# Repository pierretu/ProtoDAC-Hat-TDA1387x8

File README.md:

# ProtoDAC Hat+ TDA1387x8 Rotary Encoder

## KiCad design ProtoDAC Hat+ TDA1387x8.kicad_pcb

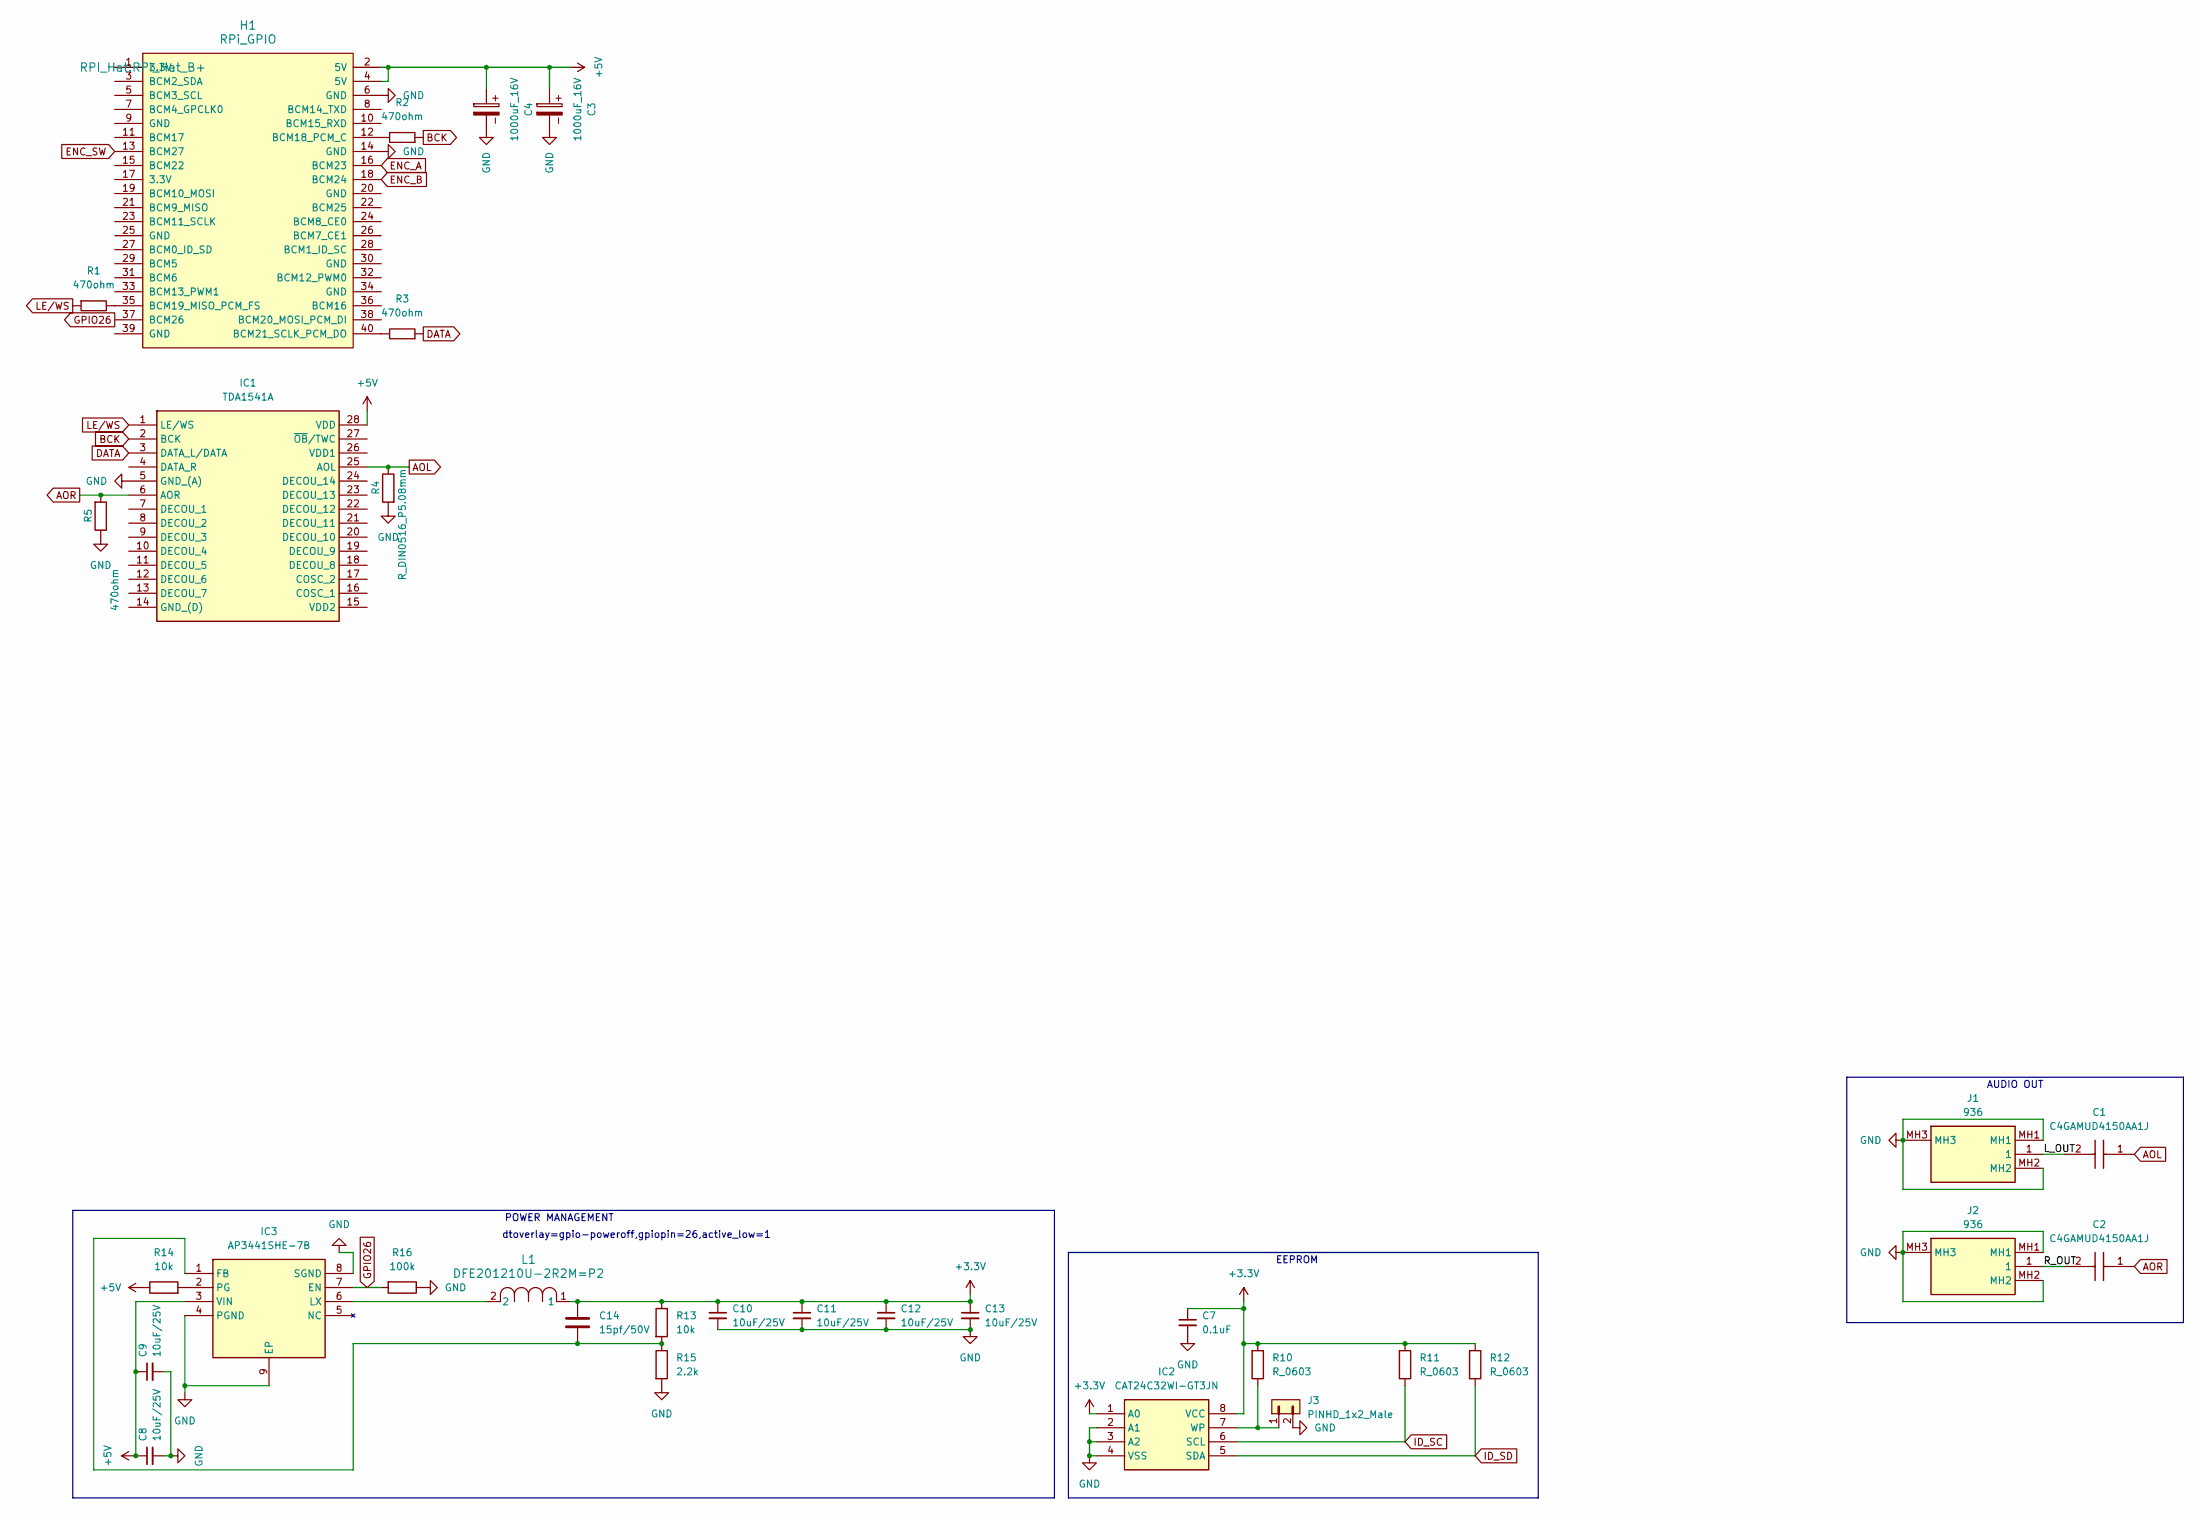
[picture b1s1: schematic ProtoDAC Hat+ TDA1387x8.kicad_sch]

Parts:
C1, C2: C4GAMUD4150AA1J; CAPPA14200W120L4400D2450; Manufacturer_Part_Number C4GAMUD4150AA1J
C3, C4: 1000uF_16V; CP_Radial_D10.0mm_P5.00mm
C7: 0.1uF_0603_16V; C_0603_1608Metric; Part Number 0603YC104KAT2A; JLCPCB ID C14663
C8, C9, C10, C11, C12, C13: 10uF_0805_25V; C_0603_1608Metric; Part Number GRM21BR61E106MA73L; JLCPCB ID C15850
C14: 15pf/50V; C_0603_1608Metric
H1: RPi_GPIO; RPI_Hat_B+
IC1: TDA1541A; DIP1652W53P254L3550H510Q28N; Manufacturer_Part_Number TDA1541A
IC2: CAT24C32WI-GT3JN; SOIC127P600X175-8N; Manufacturer_Part_Number CAT24C32WI-GT3JN
IC3: AP3441SHE-7B; SON50P201X201X60-9N-D; Manufacturer_Part_Number AP3441SHE-7B
J1, J2: 936; Manufacturer_Part_Number 936
J3: PINHD_1x2_Male; PinHeader_1x02_P2.54mm_Vertical
L1: DFE201210U-2R2M=P2; IND_DFE201210U-2R2M=P2_MUR
R1, R2, R3: 470ohm; R_Axial_DIN0207_L6.3mm_D2.5mm_P10.16mm_Horizontal
R4: R_DIN0516_P5.08mm; R_Axial_DIN0516_L15.5mm_D5.0mm_P5.08mm_Vertical
R5: 470ohm; R_Axial_DIN0516_L15.5mm_D5.0mm_P5.08mm_Vertical
R10, R11, R12: R_0603; R_0603_1608Metric
R13, R14: 10k_0603; R_0603_1608Metric; Part Number RC0603FR-0710KL; JLCPCB ID C25804
R15: 2.2k_0603; R_0603_1608Metric; Part Number RC0603FR-072K2L; JLCPCB ID C4190
R16: 100k_0603; R_0603_1608Metric; Part Number RC0603FR-07100KL; JLCPCB ID C25803

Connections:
+3.3V: C7.1, C10.1, C11.1, C12.1, C13.1, C14.1, IC2.1 (A0), IC2.8 (VCC), L1.1, R10.1, R11.1, R12.1, R13.1
+5V: C3.1, C4.1, C8.1, C9.1, H1.2 (5V), H1.4 (5V), IC1.28 (VDD), IC3.3 (VIN), R14.1
/L_OUT: C1.2 (-), J1.1
/R_OUT: C2.2 (-), J2.1
AOL: C1.1 (+), IC1.25 (AOL), R4.2
AOR: C2.1 (+), IC1.6 (AOR), R5.1
BCK: IC1.2 (BCK), R2.1
DATA: IC1.3 (DATA_L/DATA), R3.1
ENC_A: H1.16 (BCM23)
ENC_B: H1.18 (BCM24)
ENC_SW: H1.13 (BCM27)
GND: C3.2, C4.2, C7.2, C8.2, C9.2, C10.2, C11.2, C12.2, C13.2, H1.6 (GND), H1.14 (GND), IC1.5 (GND_(A)), IC2.2 (A1), IC2.3 (A2), IC2.4 (VSS), IC3.4 (PGND), IC3.8 (SGND), IC3.9 (EP), J1.MH1, J1.MH2, J1.MH3, J2.MH1, J2.MH2, J2.MH3, J3.2, R4.1, R5.2, R15.2, R16.1
GPIO26: H1.37 (BCM26), IC3.7 (EN), R16.2
ID_SC: IC2.6 (SCL), R11.2
ID_SD: IC2.5 (SDA), R12.2
LE/WS: IC1.1 (LE/WS), R1.1
unnamed: H1.12 (BCM18_PCM_C), R2.2
unnamed: H1.35 (BCM19_MISO_PCM_FS), R1.2
unnamed: H1.40 (BCM21_SCLK_PCM_DO), R3.2
unnamed: IC2.7 (WP), J3.1, R10.2
unnamed: C14.2, IC3.1 (FB), R13.2, R15.1
unnamed: IC3.6 (LX), L1.2
unnamed: IC3.2 (PG), R14.2

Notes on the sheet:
EEPROM
dtoverlay=gpio-poweroff,gpiopin=26,active_low=1
POWER MANAGEMENT
AUDIO OUT

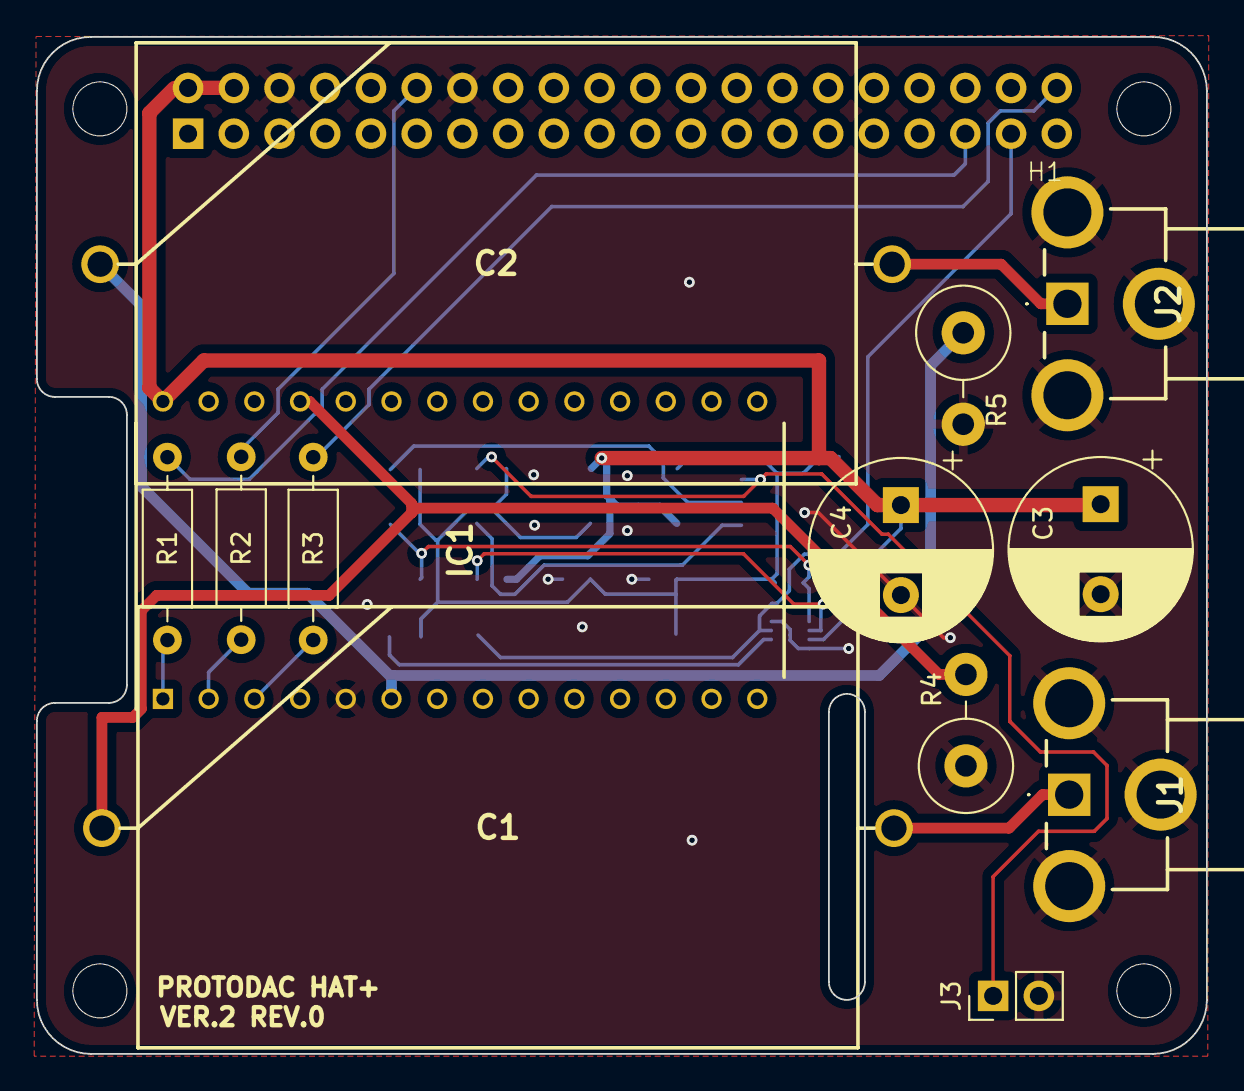
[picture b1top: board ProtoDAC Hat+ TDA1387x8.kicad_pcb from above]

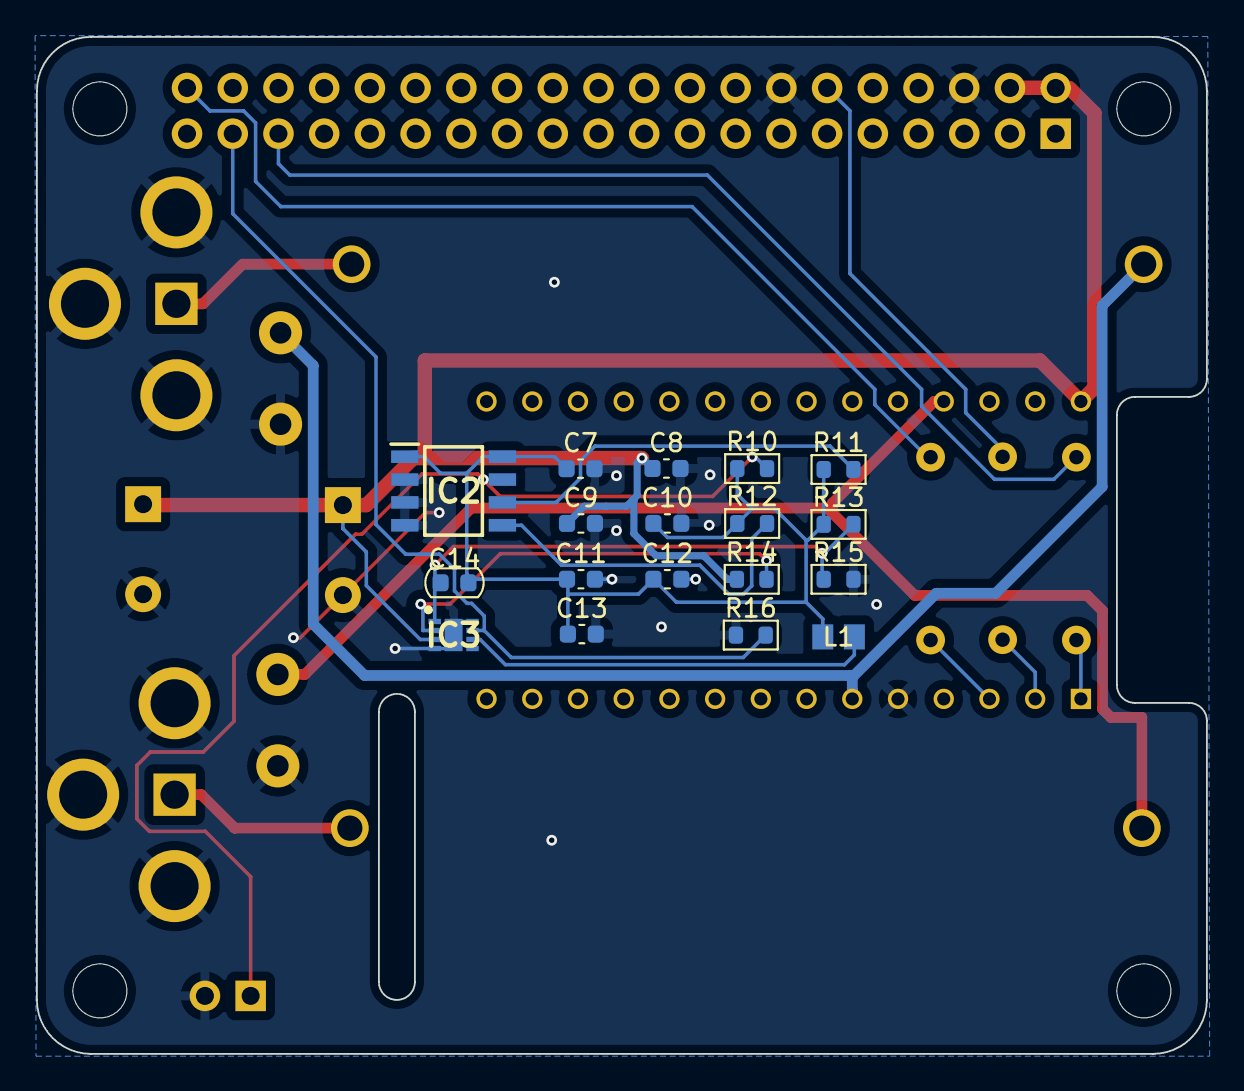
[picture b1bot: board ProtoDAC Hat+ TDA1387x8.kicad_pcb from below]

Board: 2 copper layers, 65.0 x 56.5 mm, 32 parts (18 on the bottom side), 20 nets.

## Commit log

2024-11-10 Initial release
